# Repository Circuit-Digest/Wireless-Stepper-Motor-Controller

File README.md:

# Wireless-Stepper-Motor-Controller
The Wireless Stepper Driver is a compact and efficient motion control system designed to control stepper motors over Wi-Fi.

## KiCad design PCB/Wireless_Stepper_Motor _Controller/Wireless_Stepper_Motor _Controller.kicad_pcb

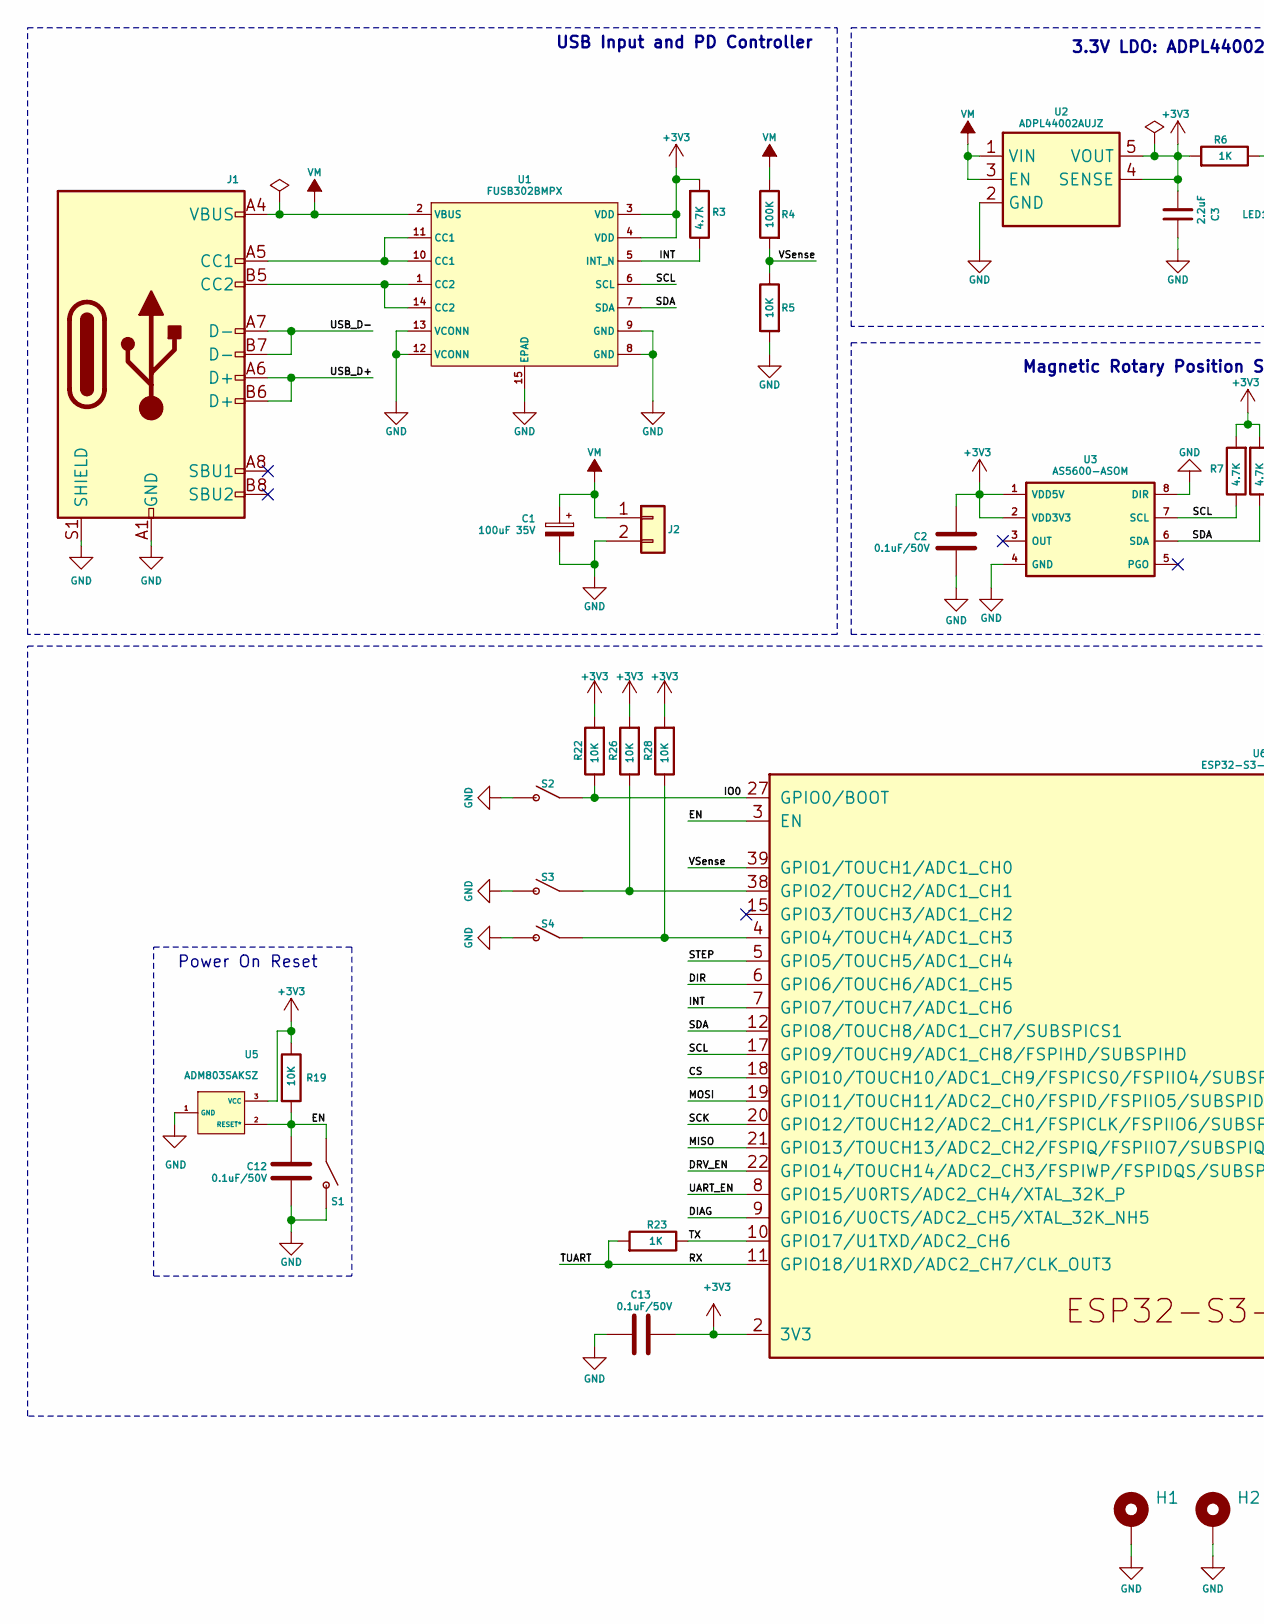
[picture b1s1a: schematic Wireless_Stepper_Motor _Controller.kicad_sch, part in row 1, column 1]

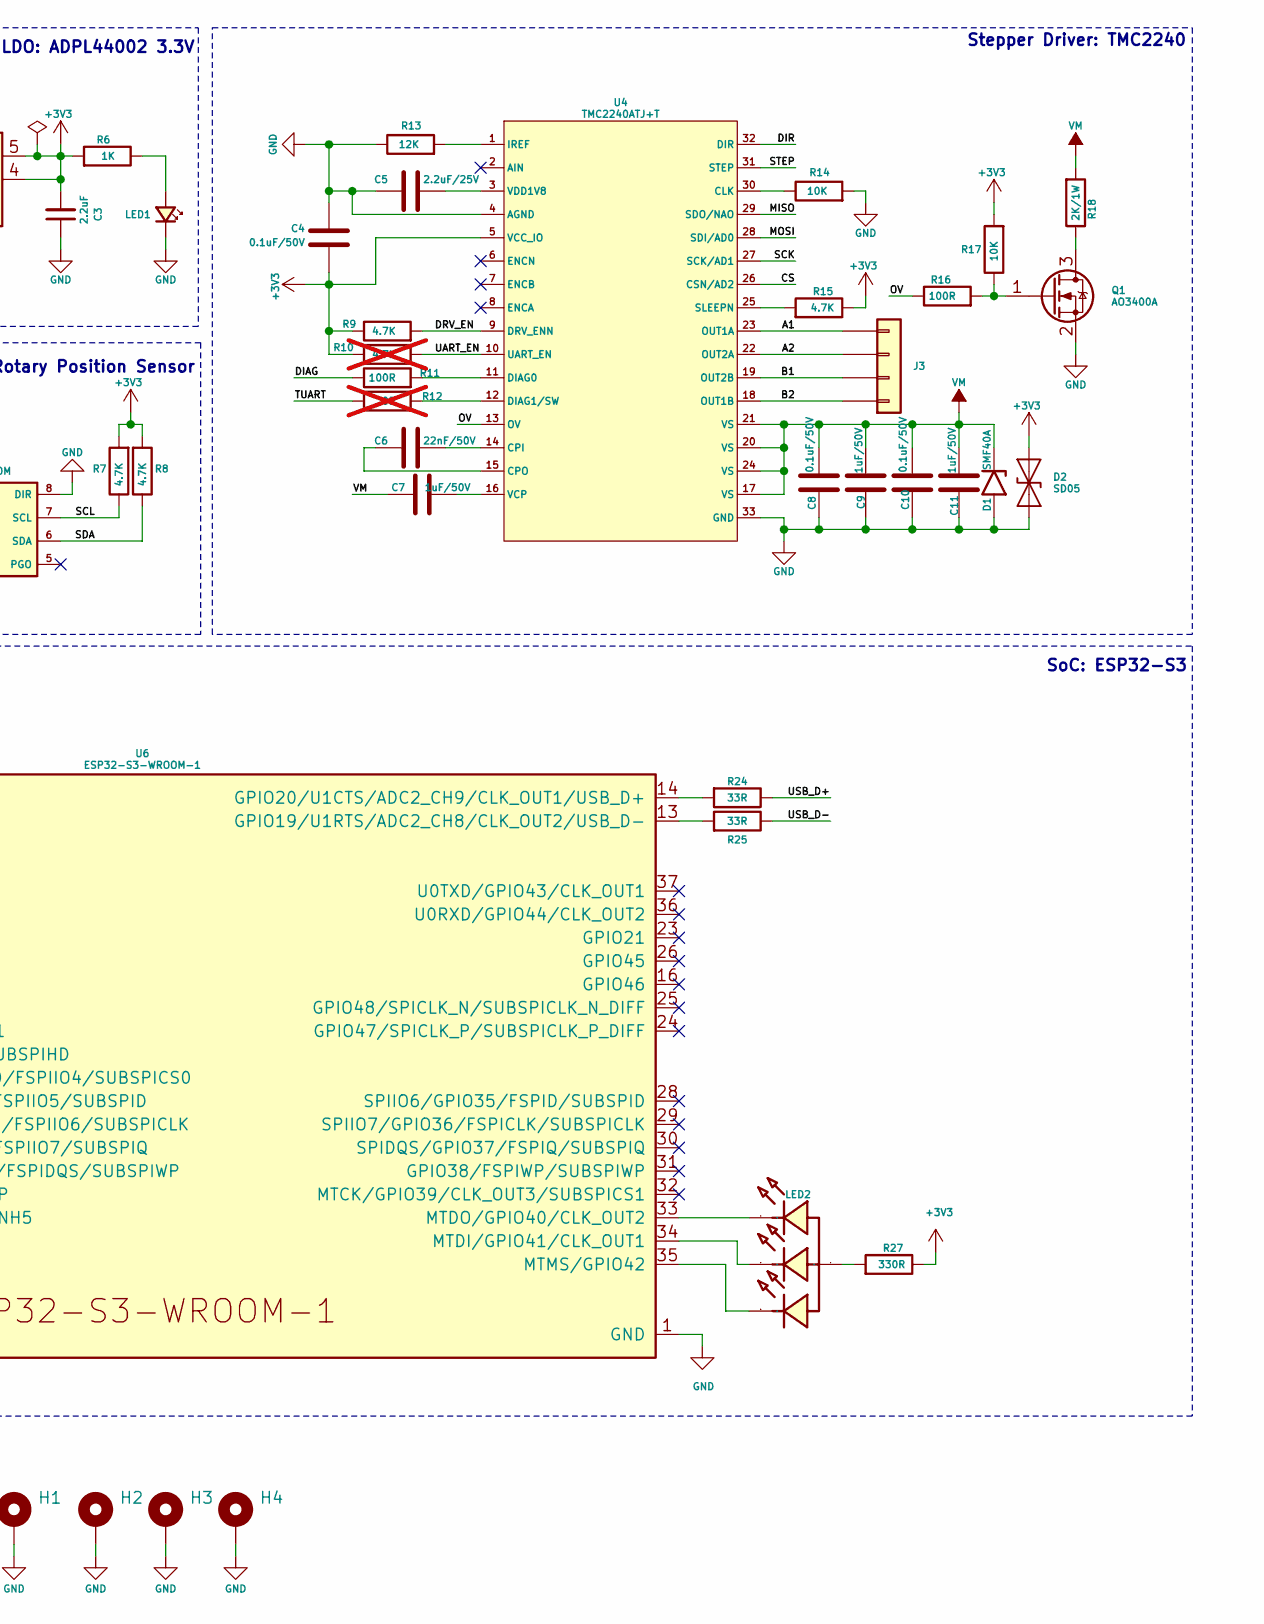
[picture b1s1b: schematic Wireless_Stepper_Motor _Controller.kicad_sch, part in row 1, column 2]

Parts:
C1: 100uF 35V; CP_Elec_6.3x5.4
C2, C4, C8, C10, C12, C13: 0.1uF/50V; C_0603_1608Metric; DigiKey Part Number 490-6328-1-ND
C3: 2.2uF; C_0603_1608Metric
C5: 2.2uF/25V; C_0603_1608Metric; DigiKey Part Number 490-6328-1-ND
C6: 22nF/50V; C_0603_1608Metric; DigiKey Part Number 490-6328-1-ND
C7, C9, C11: 1uF/50V; C_0603_1608Metric; DigiKey Part Number 490-6328-1-ND
D1: SMF40A; D_SMF
D2: SD05; D_SOD-323
H1, H2, H3, H4: MountingHole_Pad; MountingHole_3.2mm_M3_Pad_Via
J1: USB_C_Receptacle_USB2.0; USB_C_Receptacle_XKB_U262-16XN-4BVC11; DigiKey Part Number 2073-USB4105-GF-ACT-ND
J2: Conn_01x02; PinHeader_1x02_P2.54mm_Vertical
J3: Conn_01x04; JST_PH_S4B-PH-K_1x04_P2.00mm_Horizontal
LED1: LED_Small; LED_0603_1608Metric
LED2: XL-1615RGBC-YG; LED-SMD_4P-L1.6-W1.5-BL-2; Manufacturer Part XL-1615RGBC-YG
Q1: AO3400A; SOT-23
R3, R7, R8, R9, R15: 4.7K; R_0603_1608Metric; DigiKey Part Number P10.0KHCT-ND
R4: 100K; R_0603_1608Metric; DigiKey Part Number P5.10KHCT-ND
R5: 10K; R_0603_1608Metric; DigiKey Part Number P5.10KHCT-ND
R6, R23: 1K; R_0603_1608Metric; DigiKey Part Number P10.0KHCT-ND
R10: 4.7K; R_0603_1608Metric; DigiKey Part Number P10.0KHCT-ND; not fitted
R11, R16: 100R; R_0603_1608Metric; DigiKey Part Number P10.0KHCT-ND
R12: 0R; R_0603_1608Metric; DigiKey Part Number P10.0KHCT-ND; not fitted
R13: 12K; R_0603_1608Metric; DigiKey Part Number P10.0KHCT-ND
R14, R17, R19, R22, R26, R28: 10K; R_0603_1608Metric; DigiKey Part Number P10.0KHCT-ND
R18: 2K/1W; R_1206_3216Metric; DigiKey Part Number P10.0KHCT-ND
R24, R25: 33R; R_0603_1608Metric; DigiKey Part Number P17467CT-ND
R27: 330R; R_0603_1608Metric; DigiKey Part Number P10.0KHCT-ND
S1, S2, S3, S4: EVQ-P7A01P; SW_EVQ-P7A01P; PARTREV 2022.4
U1: FUSB302BMPX; MLP14_2P5X2P5_ONS
U2: ADPL44002AUJZ; SOT95P280X100-5N; Manufacturer_Part_Number ADPL44002AUJZ2.5-R7
U3: AS5600-ASOM; SOIC127P600X175-8N; Mouser Part Number 985-AS5600-ASOM
U4: TMC2240ATJ+T; 21-0140_T3255&plus_5C_TRI
U5: ADM803SAKSZ; KS_3_ADI; DigiKey Part Number 505-ADM803SAKSZ-REEL7CT-ND
U6: ESP32-S3-WROOM-1; ESP32-S3-WROOM-1U; DigiKey Part Number 1965-ESP32-S3-WROOM-1-N16R8CT-ND

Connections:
+3V3: C2.1, C3.2, C4.2, C13.1, D2.1 (A1), R3.2, R6.2, R7.2, R8.2, R9.1, R10.1, R15.1, R17.2, R19.1, R22.2, R26.2, R27.1, R28.2, U1.3 (VDD), U1.4 (VDD), U2.4 (SENSE), U2.5 (VOUT), U3.1 (VDD5V), U3.2 (VDD3V3), U4.5 (VCC_IO), U5.3 (VCC), U6.2 (3V3)
/A1: J3.4, U4.23 (OUT1A)
/A2: J3.3, U4.22 (OUT2A)
/B1: J3.2, U4.19 (OUT2B)
/B2: J3.1, U4.18 (OUT1B)
/CS: U4.26 (CSN/AD2), U6.18 (GPIO10/TOUCH10/ADC1_CH9/FSPICS0/FSPIIO4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)
/DIAG: R11.1, U6.9 (GPIO16/U0CTS/ADC2_CH5/XTAL_32K_NH5)
/DIR: U4.32 (DIR), U6.6 (GPIO6/TOUCH6/ADC1_CH5)
/DRV_EN: R9.2, U4.9 (DRV_ENN), U6.22 (GPIO14/TOUCH14/ADC2_CH3/FSPIWP/FSPIDQS/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)
/EN: C12.1, R19.2, S1.1_1, S1.1_2, U5.2 (RESET*), U6.3 (EN)
/INT: R3.1, U1.5 (INT_N), U6.7 (GPIO7/TOUCH7/ADC1_CH6)
/IO0: R22.1, S2.1_1, S2.1_2, U6.27 (GPIO0/BOOT)
/MISO: U4.29 (SDO/NAO), U6.21 (GPIO13/TOUCH13/ADC2_CH2/FSPIQ/FSPIIO7/S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)
/MOSI: U4.28 (SDI/AD0), U6.19 (GPIO11/TOUCH11/ADC2_CH0/FSPID/FSPIIO5/S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)
/OV: R16.1, U4.13 (OV)
/RX: R12.1, R23.2, U6.11 (GPIO18/U1RXD/ADC2_CH7/CLK_OUT3)
/SCK: U4.27 (SCK/AD1), U6.20 (GPIO12/TOUCH12/ADC2_CH1/FSPICLK/FSPIIO6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)
/SCL: R7.1, U1.6 (SCL), U3.7 (SCL), U6.17 (GPIO9/TOUCH9/ADC1_CH8/FSPIHD/SUBSPIHD)
/SDA: R8.1, U1.7 (SDA), U3.6 (SDA), U6.12 (GPIO8/TOUCH8/ADC1_CH7/SUBSPICS1)
/STEP: U4.31 (STEP), U6.5 (GPIO5/TOUCH5/ADC1_CH4)
/TX: R23.1, U6.10 (GPIO17/U1TXD/ADC2_CH6)
/UART_EN: R10.2, U4.10 (UART_EN), U6.8 (GPIO15/U0RTS/ADC2_CH4/XTAL_32K_P)
/USB_D+: J1.A6 (D+), J1.B6 (D+), R24.1
/USB_D-: J1.A7 (D-), J1.B7 (D-), R25.1
/VSense: R4.2, R5.1, U6.39 (GPIO1/TOUCH1/ADC1_CH0)
GND: C1.2, C2.2, C3.1, C4.1, C5.2, C8.2, C9.1, C10.2, C11.1, C12.2, C13.2, D1.2 (A2), D2.2 (A2), H1.1, H2.1, H3.1, H4.1, J1.A1 (GND), J1.A12 (GND), J1.B1 (GND), J1.B12 (GND), J1.S1 (SHIELD), J2.2, LED1.1 (K), Q1.2 (S), R5.2, R13.1, R14.2, S1.2_1, S1.2_2, S2.2_1, S2.2_2, S3.2_1, S3.2_2, S4.2_1, S4.2_2, U1.8 (GND), U1.9 (GND), U1.12 (VCONN), U1.13 (VCONN), U1.15 (EPAD), U2.2 (GND), U3.4 (GND), U3.8 (DIR), U4.4 (AGND), U4.33 (GND), U5.1 (GND), U6.1 (GND), U6.40 (GND), U6.41 (GND)
unnamed: J1.A5 (CC1), U1.10 (CC1), U1.11 (CC1)
unnamed: J1.B5 (CC2), U1.1 (CC2), U1.14 (CC2)
unnamed: LED1.2 (A), R6.1
unnamed: LED2.1 (A), R27.2
unnamed: Q1.3 (D), R18.1
unnamed: Q1.1 (G), R16.2, R17.1
unnamed: R14.1, U4.30 (CLK)
unnamed: C6.1, U4.14 (CPI)
unnamed: C6.2, U4.15 (CPO)
unnamed: R11.2, U4.11 (DIAG0)
unnamed: R12.2, U4.12 (DIAG1/SW)
unnamed: R13.2, U4.1 (IREF)
unnamed: R15.2, U4.25 (SLEEPN)
unnamed: C7.2, U4.16 (VCP)
unnamed: C5.1, U4.3 (VDD1V8)
unnamed: R26.1, S3.1_1, S3.1_2, U6.38 (GPIO2/TOUCH2/ADC1_CH1)
unnamed: R28.1, S4.1_1, S4.1_2, U6.4 (GPIO4/TOUCH4/ADC1_CH3)
unnamed: R25.2, U6.13 (GPIO19/U1RTS/ADC2_CH8/CLK_OUT2/USB_D-)
unnamed: R24.2, U6.14 (GPIO20/U1CTS/ADC2_CH9/CLK_OUT1/USB_D+)
unnamed: LED2.3 (K), U6.34 (MTDI/GPIO41/CLK_OUT1)
unnamed: LED2.2 (K), U6.33 (MTDO/GPIO40/CLK_OUT2)
unnamed: LED2.4 (K), U6.35 (MTMS/GPIO42)
VM: C1.1, C7.1, C8.1, C9.2, C10.1, C11.2, D1.1 (A1), J1.A4 (VBUS), J1.A9 (VBUS), J1.B4 (VBUS), J1.B9 (VBUS), J2.1, R4.1, R18.2, U1.2 (VBUS), U2.1 (VIN), U2.3 (EN), U4.17 (VS), U4.20 (VS), U4.21 (VS), U4.24 (VS)

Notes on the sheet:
3.3V LDO: ADPL44002 3.3V
Power On Reset
Stepper Driver: TMC2240
Magnetic Rotary Position Sensor
SoC: ESP32-S3
USB Input and PD Controller

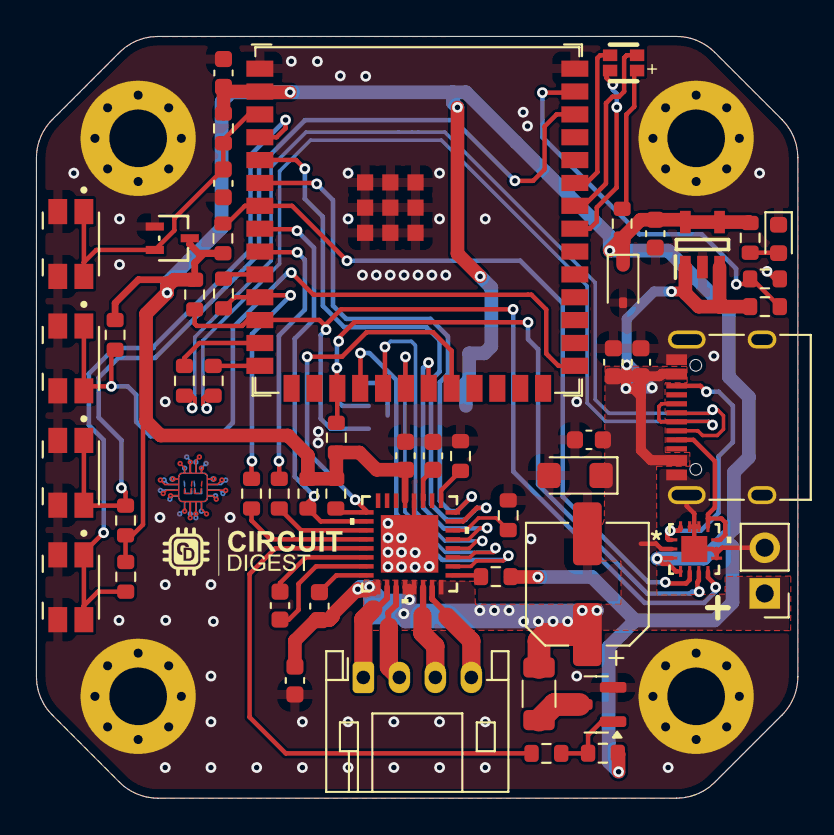
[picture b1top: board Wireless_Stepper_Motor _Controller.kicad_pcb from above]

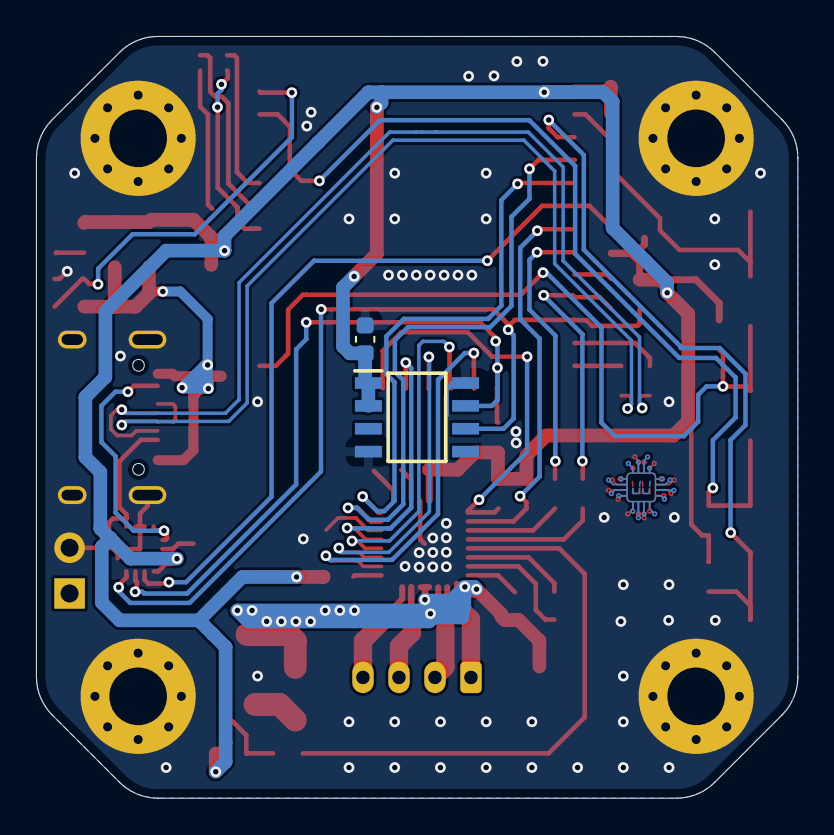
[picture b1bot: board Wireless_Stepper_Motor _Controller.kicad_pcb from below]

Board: 2 copper layers, 42.3 x 42.3 mm, 59 parts (2 on the bottom side), 49 nets.

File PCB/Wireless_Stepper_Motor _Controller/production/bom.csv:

Designator,Footprint,Quantity,Value,LCSC Part #
C1,CP_Elec_6.3x5.4,1,100uF 35V,
"C10, C12, C13, C2, C4, C8",0603,6,0.1uF/50V,
"C11, C7, C9",0603,3,1uF/50V,
C3,0603,1,2.2uF,
C5,0603,1,2.2uF/25V,
C6,0603,1,22nF/50V,
D1,D_SMF,1,SMF40A,
D2,D_SOD-323,1,SD05,
J1,USB_C_Receptacle_XKB_U262-16XN-4BVC11,1,USB_C_Receptacle_USB2.0,
J2,PinHeader_1x02_P2.54mm_Vertical,1,Conn_01x02,
J3,JST_PH_S4B-PH-K_1x04_P2.00mm_Horizontal,1,Conn_01x04,
LED1,0603,1,LED_Small,
LED2,LED-SMD_4P-L1.6-W1.5-BL-2,1,XL-1615RGBC-YG,
Q1,SOT-23,1,AO3400A,
"R10, R15, R3, R7, R8, R9",0603,6,4.7K,
"R11, R16",0603,2,100R,
R12,0603,1,0R,
R13,0603,1,12K,
"R14, R17, R19, R22, R26, R28, R5",0603,7,10K,
R18,1206,1,2K/1W,
"R23, R6",0603,2,1K,
"R24, R25",0603,2,33R,
R27,0603,1,330R,
R4,0603,1,100K,
"S1, S2, S3, S4",SW_EVQ-P7A01P,4,EVQ-P7A01P,
U1,MLP14_2P5X2P5_ONS,1,FUSB302BMPX,
U2,SOT95P280X100-5N,1,ADPL44002AUJZ,
U3,SOIC127P600X175-8N,1,AS5600-ASOM,
U4,21-0140_T3255&plus_5C_TRI,1,TMC2240ATJ+T,
U5,KS_3_ADI,1,ADM803SAKSZ,
U6,ESP32-S3-WROOM-1U,1,ESP32-S3-WROOM-1,
